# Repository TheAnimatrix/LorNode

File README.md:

# Low Cost LoRA + ESP32 Board
**This page is a work in progress!**

## Features:
- Based on RA-01 and ESP32 WROOM Modules
- Small form factor (73x43 mm)
- Double LDO Setup to decrease current usage
- Direct USB Programming w/ CH340C
- Battery charging + Protection
	- Allows the use of cheaper batteries
- Onboard RGB LED
- Low quiescent current (upto 10uA) or Lower!
- Easily available BOM
- Low Cost
	- Easy to manufacture (2 layer pcb)
	- Single side part assembly
	- Easy to assemble parts (no QFN or similar packages)

## TODO:
- Final PCB Check
- PCB Fabrication
- Searchable PDF Schematic
- clean up BOM
- Quiescent current graphs/tests

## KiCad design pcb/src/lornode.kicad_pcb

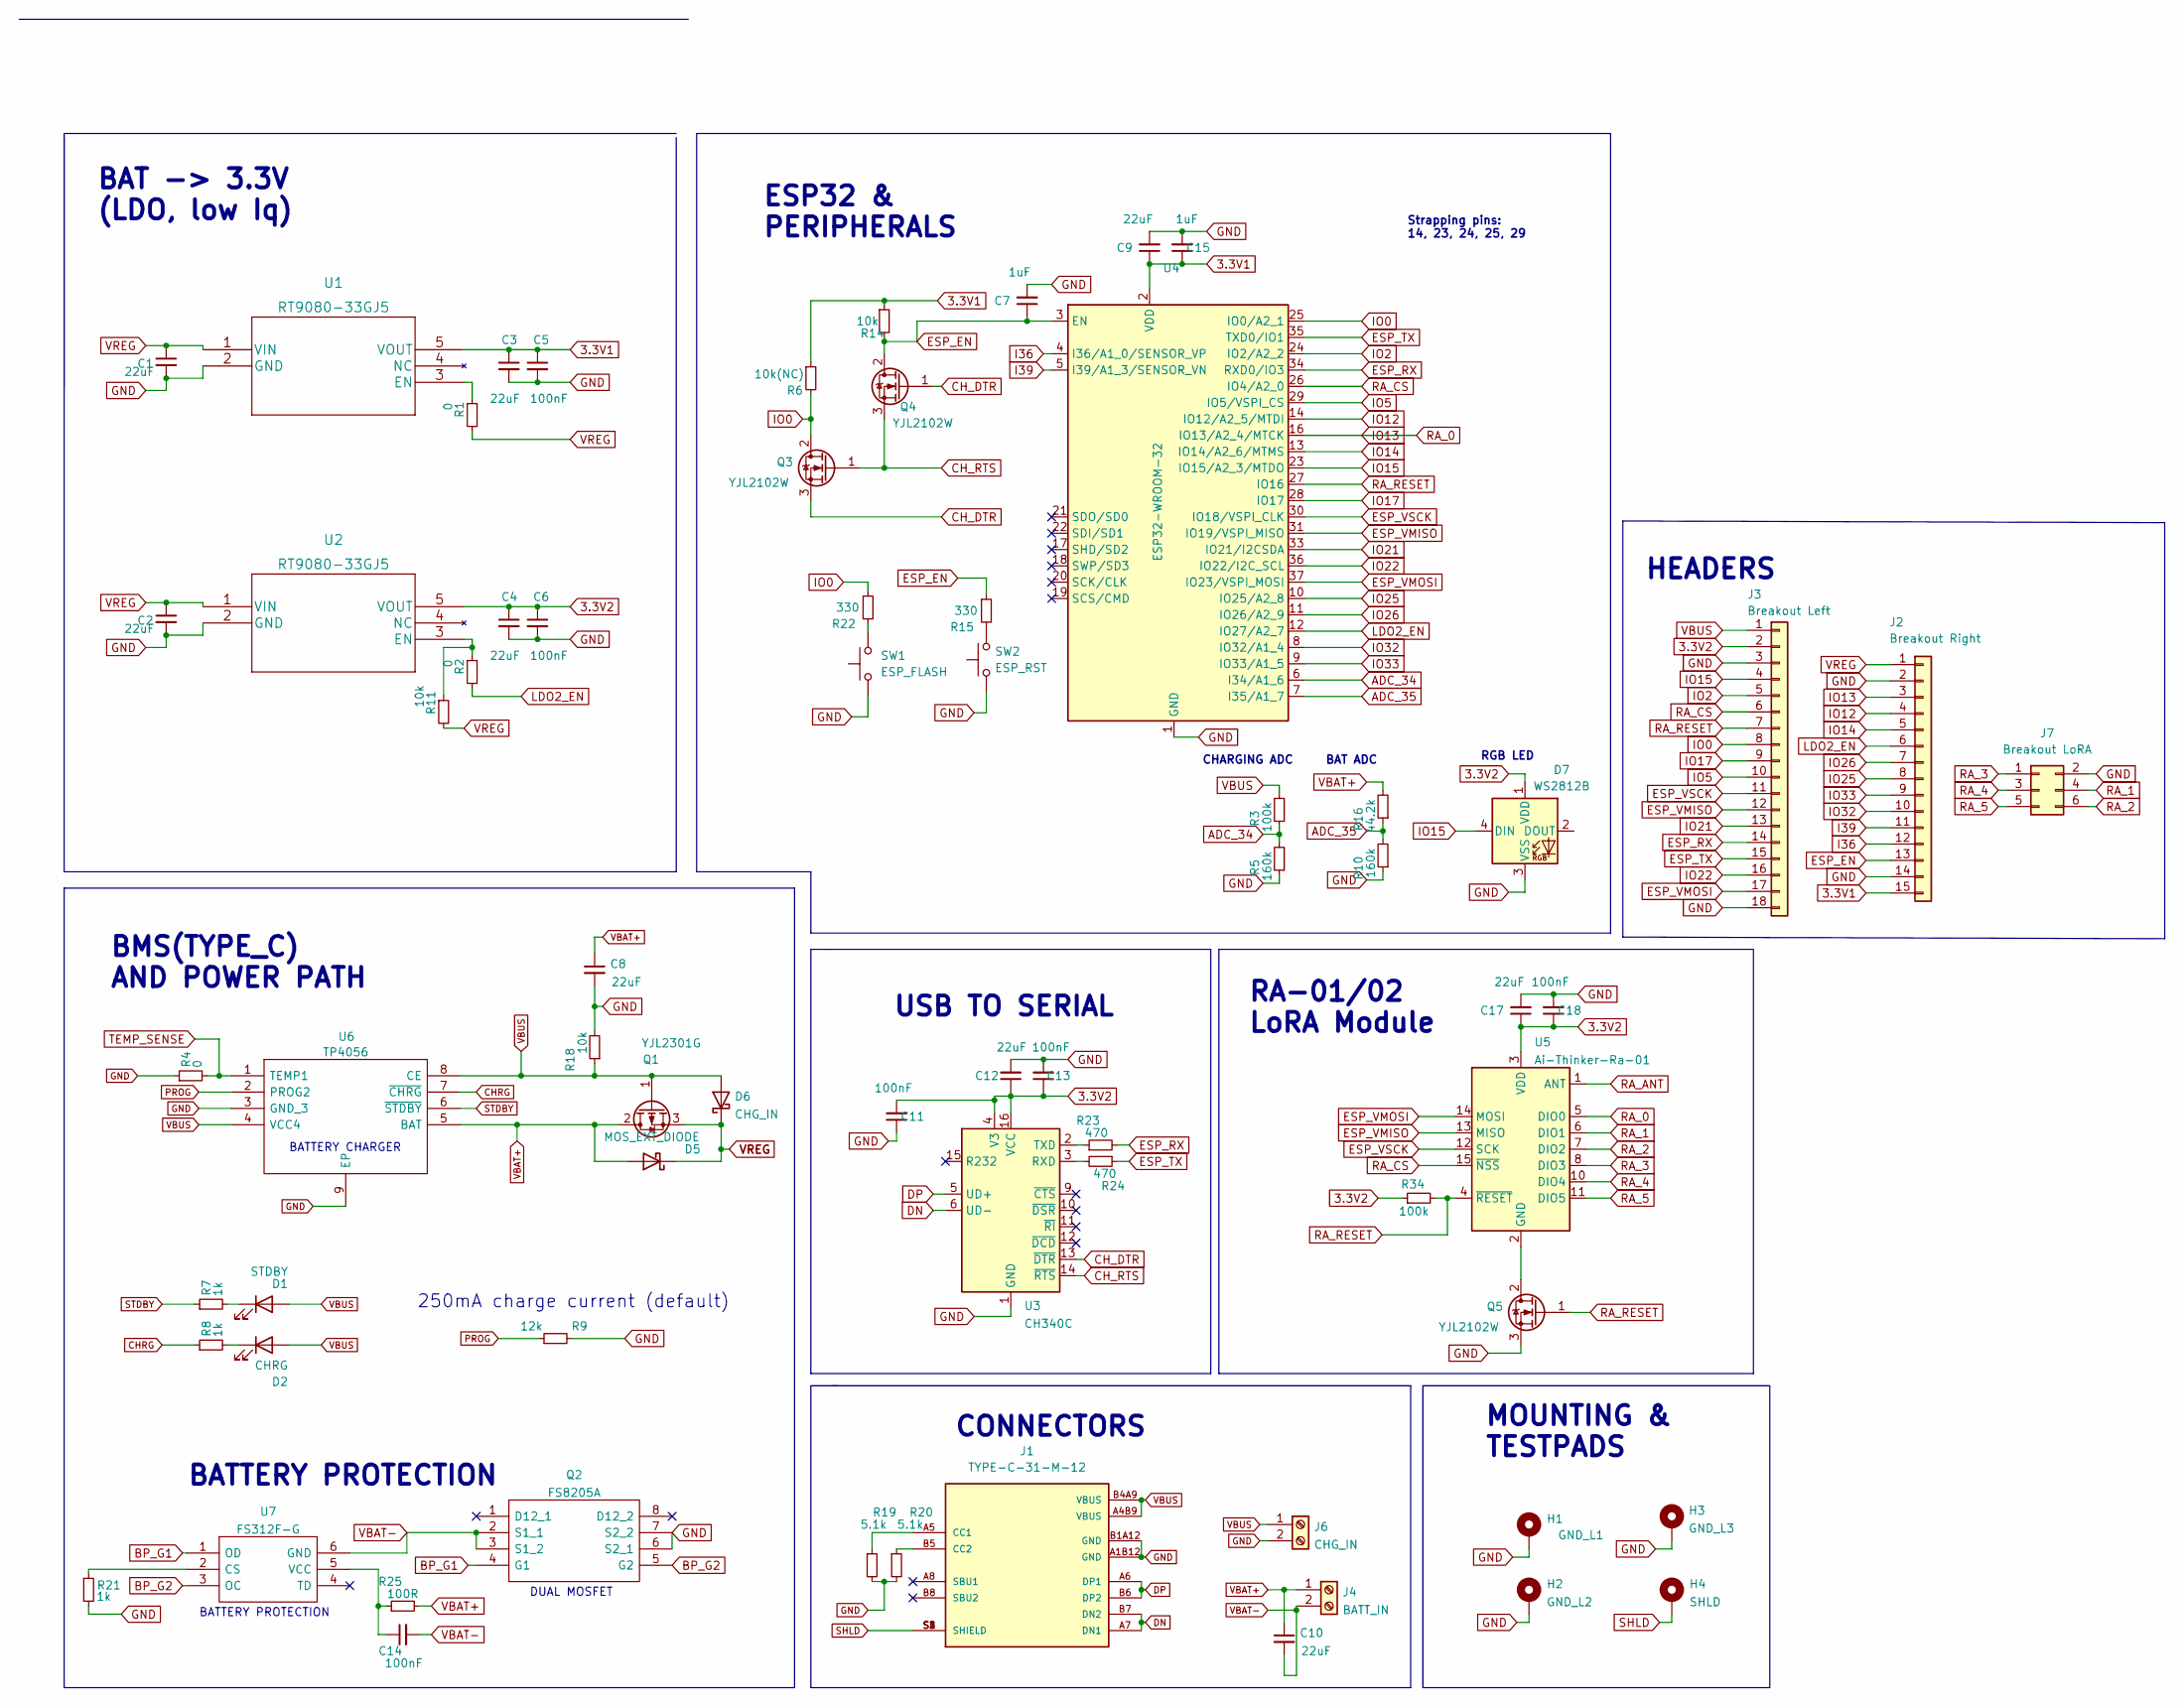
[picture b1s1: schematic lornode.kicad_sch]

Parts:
C1, C2, C3, C4, C8, C9, C10, C12, C17: 22uF; C_0805_2012Metric
C5, C6, C11, C13, C14, C18: 100nF; C_0603_1608Metric
C7, C15: 1uF; C_0603_1608Metric
D1: STDBY; LED_0805_2012Metric
D2: CHRG; LED_0805_2012Metric
D5: MOS_EXT_DIODE; DIOM5026X262N
D6: CHG_IN; DIOM5026X262N
D7: WS2812B; LED_WS2812B_PLCC4_5.0x5.0mm_P3.2mm
H1: GND_L1; MountingHole_3.2mm_M3_Pad
H2: GND_L2; MountingHole_3.2mm_M3_Pad
H3: GND_L3; MountingHole_3.2mm_M3_Pad
H4: SHLD; MountingHole_3.2mm_M3_Pad
J1: TYPE-C-31-M-12; B_TYPE-C-31-M-12; PARTREV 2020.12.08
J2: Breakout Right; PinHeader_1x15_P2.54mm_Vertical
J3: Breakout Left; PinHeader_1x18_P2.54mm_Vertical
J4: BATT_IN; TerminalBlock_Phoenix_PT-1,5-2-3.5-H_1x02_P3.50mm_Horizontal
J6: CHG_IN; TerminalBlock_Phoenix_PT-1,5-2-3.5-H_1x02_P3.50mm_Horizontal
J7: Breakout LoRA; PinHeader_2x03_P2.54mm_Vertical
Q1: YJL2301G; SOT-23
Q2: FS8205A; SOP65P640X120-8N; Manufacturer_Part_Number FS8205A
Q3, Q4, Q5: YJL2102W; SOT-323_SC-70
R1, R2, R4: 0; R_0603_1608Metric
R3, R34: 100k; R_0603_1608Metric
R5, R10: 160k; R_0603_1608Metric
R6: 10k(NC); R_0603_1608Metric
R7, R8, R21: 1k; R_0603_1608Metric
R9: 12k; R_0603_1608Metric
R11, R14, R18: 10k; R_0603_1608Metric
R15, R22: 330; R_0603_1608Metric
R16: 44.2k; R_0603_1608Metric
R19, R20: 5.1k; R_0603_1608Metric
R23, R24: 470; R_0603_1608Metric
R25: 100R; R_0603_1608Metric
SW1: ESP_FLASH; SKQYABE010
SW2: ESP_RST; SKQYABE010
U1, U2: RT9080-33GJ5
U3: CH340C; SOIC-16_3.9x9.9mm_P1.27mm
U4: ESP32-WROOM-32
U5: Ai-Thinker-Ra-01; Ai-Thinker-Ra-01-LoRa
U6: TP4056; SOIC127P600X175-9N; Manufacturer_Part_Number TP4056
U7: FS312F-G; SOT95P280X145-6N; Manufacturer_Part_Number FS312F-G

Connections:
3.3V1: C3.1, C5.1, C9.1, C15.1, J2.15, R6.1, R14.1, U1.5 (VOUT), U4.2 (VDD)
3.3V2: C4.1, C6.1, C11.2, C12.1, C13.1, C17.1, C18.1, D7.1 (VDD), J3.2, R34.1, U2.5 (VOUT), U3.4 (V3), U3.16 (VCC), U5.3 (VDD)
ADC_34: R3.1, R5.2, U4.6 (I34/A1_6)
ADC_35: R10.2, R16.1, U4.7 (I35/A1_7)
BP_G1: Q2.4 (G1), U7.1 (OD)
BP_G2: Q2.5 (G2), U7.3 (OC)
CHRG: R8.1, U6.7 (~CHRG)
CH_DTR: Q3.3 (S), Q4.1 (G), U3.13 (~DTR)
CH_RTS: Q3.1 (G), Q4.3 (S), U3.14 (~RTS)
DN: J1.A7 (DN1), J1.B7 (DN2), U3.6 (UD-)
DP: J1.A6 (DP1), J1.B6 (DP2), U3.5 (UD+)
ESP_EN: C7.1, J2.13, Q4.2 (D), R14.2, R15.1, U4.3 (EN)
ESP_RX: J3.14, R23.2, U4.34 (RXD0/IO3)
ESP_TX: J3.15, R24.1, U4.35 (TXD0/IO1)
ESP_VMISO: J3.12, U4.31 (IO19/VSPI_MISO), U5.13 (MISO)
ESP_VMOSI: J3.17, U4.37 (IO23/VSPI_MOSI), U5.14 (MOSI)
ESP_VSCK: J3.11, U4.30 (IO18/VSPI_CLK), U5.12 (SCK)
GND: C1.2, C2.2, C3.2, C4.2, C5.2, C6.2, C7.2, C8.2, C9.2, C11.1, C12.2, C13.2, C15.2, C17.2, C18.2, D7.3 (VSS), H1.1, H2.1, H3.1, J1.A1B12 (GND), J1.B1A12 (GND), J2.2, J2.14, J3.3, J3.18, J6.2, J7.2, Q2.6 (S2_1), Q2.7 (S2_2), Q5.3 (S), R4.1, R5.1, R9.2, R10.1, R18.2, R19.2, R20.2, R21.2, SW1.1, SW2.1, U1.2 (GND), U2.2 (GND), U3.1 (GND), U4.1 (GND), U4.15 (GND), U4.38 (GND), U4.39 (GND), U6.3 (GND_3), U6.9 (EP)
I36: J2.12, U4.4 (I36/A1_0/SENSOR_VP)
I39: J2.11, U4.5 (I39/A1_3/SENSOR_VN)
IO0: J3.8, Q3.2 (D), R6.2, R22.1, U4.25 (IO0/A2_1)
IO2: J3.5, U4.24 (IO2/A2_2)
IO5: J3.10, U4.29 (IO5/VSPI_CS)
IO12: J2.4, U4.14 (IO12/A2_5/MTDI)
IO13: J2.3, U4.16 (IO13/A2_4/MTCK), U5.5 (DIO0)
IO14: J2.5, U4.13 (IO14/A2_6/MTMS)
IO15: D7.4 (DIN), J3.4, U4.23 (IO15/A2_3/MTDO)
IO17: J3.9, U4.28 (IO17)
IO21: J3.13, U4.33 (IO21/I2CSDA)
IO22: J3.16, U4.36 (IO22/I2C_SCL)
IO25: J2.8, U4.10 (IO25/A2_8)
IO26: J2.7, U4.11 (IO26/A2_9)
IO32: J2.10, U4.8 (IO32/A1_4)
IO33: J2.9, U4.9 (IO33/A1_5)
LDO2_EN: J2.6, R2.2, U4.12 (IO27/A2_7)
unnamed: C14.1, R25.1, U7.5 (VCC)
unnamed: D1.1 (K), R7.2
unnamed: D2.1 (K), R8.2
unnamed: J1.A5 (CC1), R19.1
unnamed: J1.B5 (CC2), R20.1
unnamed: Q5.2 (D), U5.2 (GND), U5.9 (GND), U5.16 (GND)
unnamed: R1.1, U1.3 (EN)
unnamed: R2.1, R11.1, U2.3 (EN)
unnamed: R15.2, SW2.2
unnamed: R21.1, U7.2 (CS)
unnamed: R22.2, SW1.2
unnamed: R23.1, U3.2 (TXD)
unnamed: R24.2, U3.3 (RXD)
PROG: R9.1, U6.2 (PROG2)
RA_1: J7.4, U5.6 (DIO1)
RA_2: J7.6, U5.7 (DIO2)
RA_3: J7.1, U5.8 (DIO3)
RA_4: J7.3, U5.10 (DIO4)
RA_5: J7.5, U5.11 (DIO5)
RA_ANT: U5.1 (ANT)
RA_CS: J3.6, U4.26 (IO4/A2_0), U5.15 (~NSS)
RA_RESET: J3.7, Q5.1 (G), R34.2, U4.27 (IO16), U5.4 (~RESET)
SHLD: H4.1, J1.S1 (SHIELD), J1.S2 (SHIELD), J1.S3 (SHIELD), J1.S4 (SHIELD)
STDBY: R7.1, U6.6 (~STDBY)
TEMP_SENSE: R4.2, U6.1 (TEMP1)
VBAT+: C8.1, C10.1, D5.1 (A), J4.1, Q1.2 (D), R16.2, R25.2, U6.5 (BAT)
VBAT-: C10.2, C14.2, J4.2, Q2.2 (S1_1), Q2.3 (S1_2), U7.6 (GND)
VBUS: D1.2 (A), D2.2 (A), D6.2 (A), J1.A4B9 (VBUS), J1.B4A9 (VBUS), J3.1, J6.1, Q1.1 (G), R3.2, R18.1, U6.4 (VCC4), U6.8 (CE)
VREG: C1.1, C2.1, D5.2 (K), D6.1 (K), J2.1, Q1.3 (S), R1.2, R11.2, U1.1 (VIN), U2.1 (VIN)

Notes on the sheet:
MOUNTING & TESTPADS
BATTERY PROTECTION
RGB LED
CHARGING ADC
BAT ADC
ESP32 & PERIPHERALS
BATTERY CHARGER
RA-01/02 LoRA Module
CONNECTORS
Strapping pins: 14, 23, 24, 25, 29
BAT -> 3.3V (LDO, low Iq)
USB TO SERIAL
250mA charge current (default)
HEADERS
BMS(TYPE_C) AND POWER PATH
DUAL MOSFET

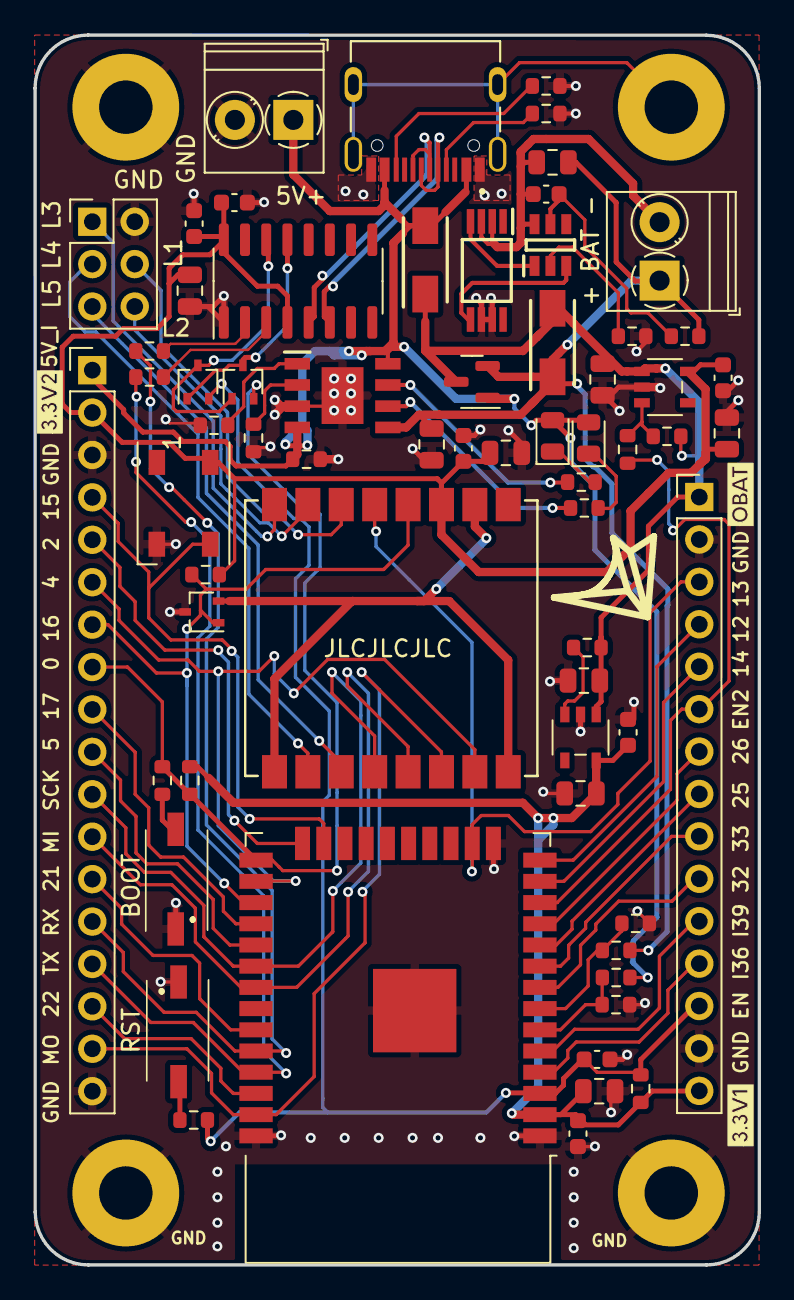
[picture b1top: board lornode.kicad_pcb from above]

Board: 2 copper layers, 43.4 x 73.7 mm, 69 parts (0 on the bottom side), 63 nets.

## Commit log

2022-10-15 genesis. Lornode V2
2022-10-15 Fixed README
2022-10-20 v2 minor updates
